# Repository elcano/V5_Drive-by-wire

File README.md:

# V5_Drive-by-wire
Updated code and PCB for light vehicle drive by wire.

This repository is for use with the **Drive by Wire** board created to be used for the ELCANO self-driving tricycle. It controls throttle (Ebike controller), brakes (solenoid) and steering (either linear servo or motor controller board with a linear actuator). All vehicle actions are logged to an SD card, which is the main data for debugging. Vehicle can be controlled by

1) 6-channel Radio Control (RC) unit

2) Operator controls (OP)

3) Vehicle automation computer via CAN. We have demonstrated a Jetson Nano using a Pixhawk to find GNSS points and move from waypoint to waypoint.

In order for this module to run external libraries are required.

Libraries needed are listed below:

Version 4 and 5 (Arduino Due)  _______________________________________________
* Due CAN and CAN Common by Collin Kidder
    https://github.com/collin80/due_can
    https://github.com/collin80/can_common

## To Install

* Download the **Drive_By_Wire** module into the project parent directory
```
git clone https://github.com/elcano/Drive-by-wire.git
```
* Move into the **Drive_By_Wire** folder
```
cd Drive_By_Wire
```
* Download the required libraries
```
git clone https://github.com/SweBarre/MCP48x2.git
git clone https://github.com/ivanseidel/DueTimer.git
git clone https://github.com/collin80/can_common.git
git clone https://github.com/collin80/due_can.git
```
* Add the folders above to the IDE directory. In Windows, add the required libraries to: C:\Users\<username>\Documents\Arduino\libraries
* Arduino Due requires additional installation. On the IDE, go to Tools -> Boards -> Boards Manager -> Arduino SAM Boards (32-bits ARM Cortex-M3) 

## Navigating Arduino IDE: 
* **Selecting Board:** Tools -> Board -> Arduino SAM Boards -> Arduino Due
* **Selecting Serial Port:** Tools -> Port -> COM (Arduino Due)
* **Accessing Serial Monitor:** Right-hand Corner -> Select Baud Rate (115200)

## Drive-by-Wire: 
* **Low-level board code with RC control support with existing code for brakes, steering, and throttle.**

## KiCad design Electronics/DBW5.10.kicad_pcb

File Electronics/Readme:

Full KiCAD project for DBW circuit board

There is a subdirectory for the power box.

The main KiCAD project has lost the link to the schematics. 
The zip file contains the three sheets of as-built schematics as Low_Level4_1_x.kicad.sch

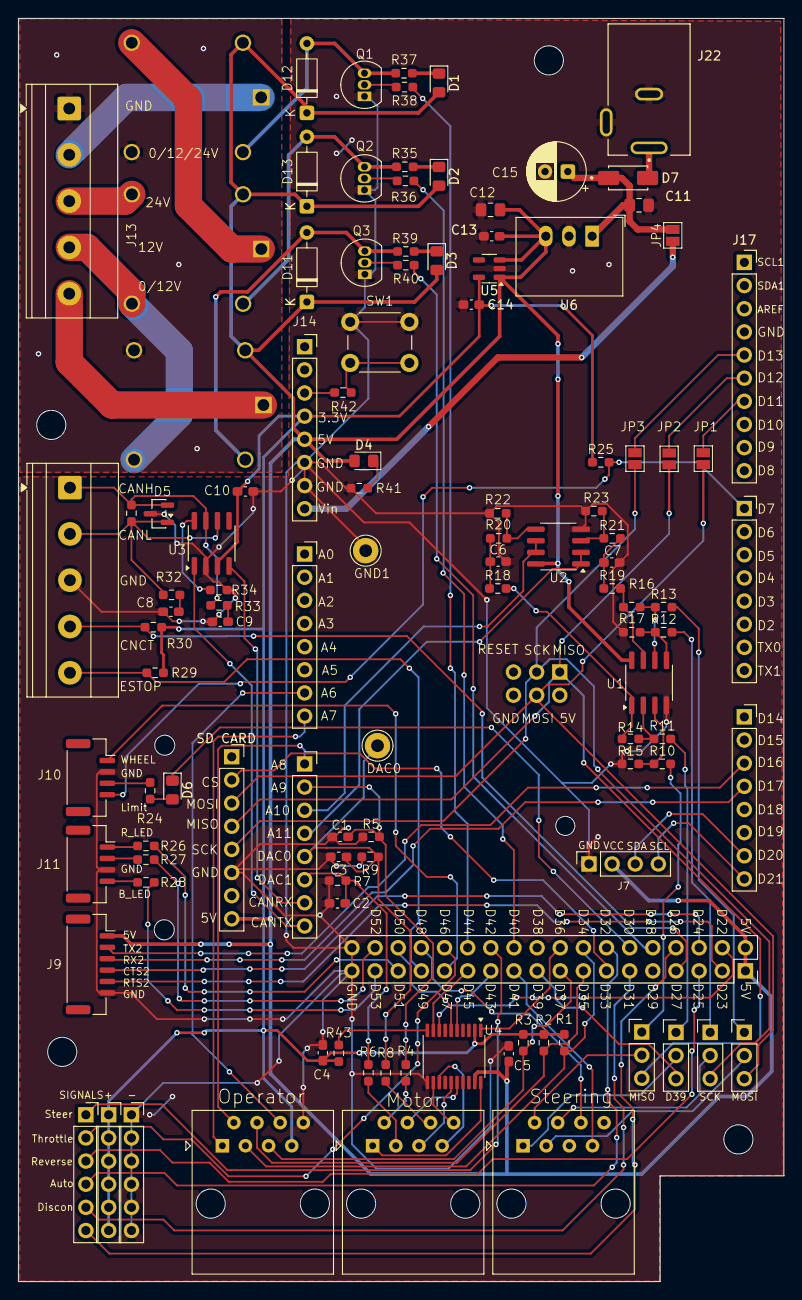
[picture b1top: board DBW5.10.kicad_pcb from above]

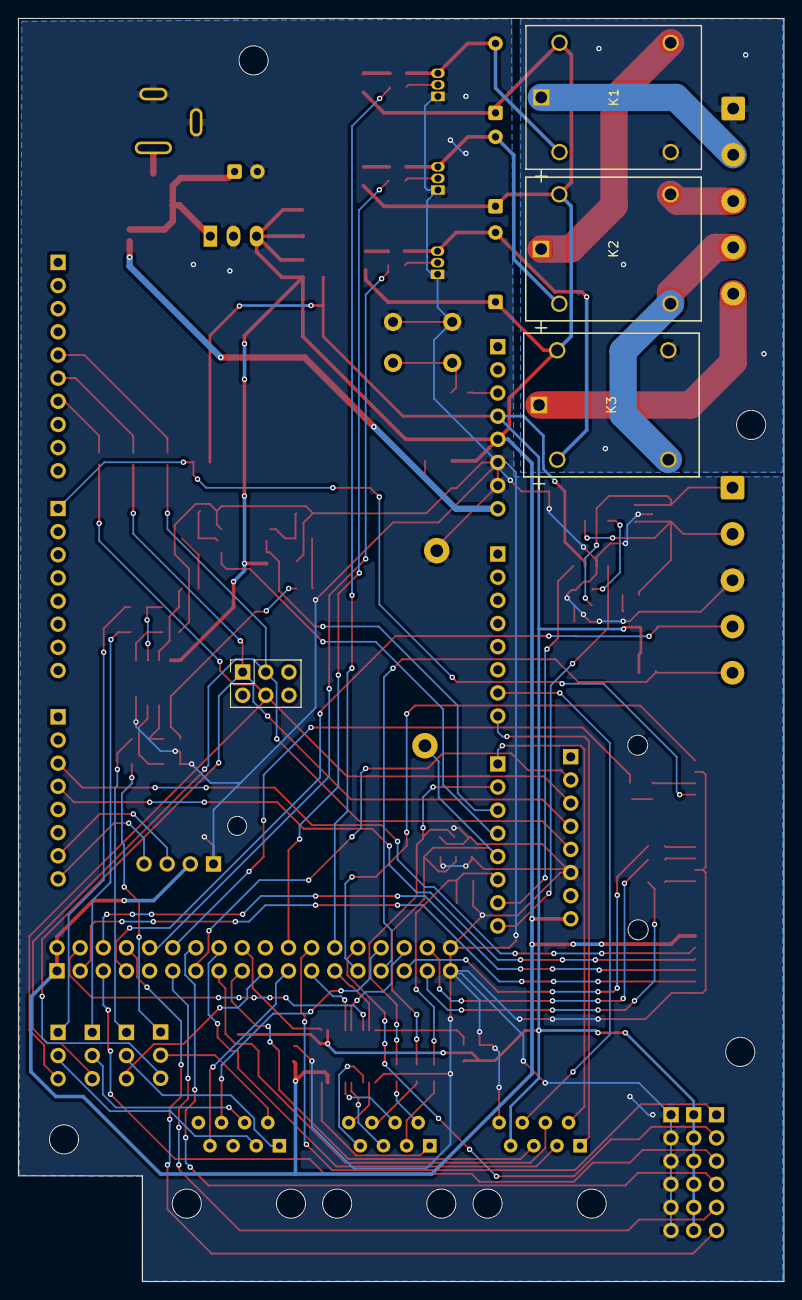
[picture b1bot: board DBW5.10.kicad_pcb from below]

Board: 2 copper layers, 84.0 x 138.6 mm, 113 parts (4 on the bottom side), 112 nets.

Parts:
C1, C2, C3, C4, C5, C10: 0.1uF; C_0603_1608Metric_Pad1.08x0.95mm_HandSolder
C6, C7: 100nF; C_0603_1608Metric_Pad1.08x0.95mm_HandSolder
C8, C9: 100pF; C_0603_1608Metric_Pad1.08x0.95mm_HandSolder
C11, C12: 10uF; C_0805_2012Metric_Pad1.18x1.45mm_HandSolder
C13, C14: 1uF; C_0603_1608Metric_Pad1.08x0.95mm_HandSolder
C15: 47uF; CP_Radial_D6.3mm_P2.50mm
D1, D2, D3: LED; LED_0805_2012Metric_Pad1.15x1.40mm_HandSolder
D4: LED_Power; LED_0805_2012Metric_Pad1.15x1.40mm_HandSolder
D5: NUP2105L; SOT-23
D6: LED_Debug; LED_0805_2012Metric_Pad1.15x1.40mm_HandSolder
D7: B140-13-F; DIOM4326X240N
D11, D12, D13: 1N4148; D_DO-35_SOD27_P7.62mm_Horizontal
DAC0: TestPoint; TestPoint_Loop_D2.60mm_Drill1.4mm_Beaded
GND1: TestPoint; TestPoint_Loop_D2.60mm_Drill1.4mm_Beaded
J1: O-RJ45; RJ45_Amphenol_54602-x08_Horizontal
J2: M-RJ45; RJ45_Amphenol_54602-x08_Horizontal
J3: S-RJ45; RJ45_Amphenol_54602-x08_Horizontal
J4, J5, J6: Conn_01x06; PinSocket_1x06_P2.54mm_Vertical
J7: Conn_01x04; PinSocket_1x04_P2.54mm_Vertical
J8, J14, J15, J16, J18, J19: Conn_01x08; PinSocket_1x08_P2.54mm_Vertical
J9: Conn_01x06; JST_GH_SM06B-GHS-TB_1x06-1MP_P1.25mm_Horizontal
J10, J11: Conn_01x04; JST_GH_SM04B-GHS-TB_1x04-1MP_P1.25mm_Horizontal
J12, J13: Screw_Terminal_01x05; TerminalBlock_Phoenix_MKDS-1,5-5-5.08_1x05_P5.08mm_Horizont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
J17: Conn_01x10; PinSocket_1x10_P2.54mm_Vertical
J20: Conn_02x18_Odd_Even; PinSocket_2x18_P2.54mm_Vertical
J21: Conn_02x03_Odd_Even; PinSocket_2x03_P2.54mm_Vertical
J22: 54-00129; TENSILITY_54-00129
JP1, JP2, JP3, JP4: Jumper_2_Open; SolderJumper-2_P1.3mm_Open_Pad1.0x1.5mm
JP5, JP6, JP7, JP8: Jumper_3_Bridged12; PinHeader_1x03_P2.54mm_Vertical
K1, K2, K3: J107F1CS125VDC.36; RELAY5_J107F-1C_CRS
Q1, Q2, Q3: 2N3904; TO-92_Inline
R1, R2, R3, R22, R23, R25, R29, R30, R34, R43: 10k; R_0603_1608Metric_Pad0.98x0.95mm_HandSolder
R4: 1.5k; R_0603_1608Metric_Pad0.98x0.95mm_HandSolder
R5: 2.7k; R_0603_1608Metric_Pad0.98x0.95mm_HandSolder
R6, R8: 15k; R_0603_1608Metric_Pad0.98x0.95mm_HandSolder
R7, R9: 27k; R_0603_1608Metric_Pad0.98x0.95mm_HandSolder
R10, R11, R12, R13, R14, R15, R16, R17: 22k; R_0603_1608Metric_Pad0.98x0.95mm_HandSolder
R18, R19, R35, R36, R37, R38, R39, R40, R41: 1k; R_0603_1608Metric_Pad0.98x0.95mm_HandSolder
R20, R21: 4.7k; R_0603_1608Metric_Pad0.98x0.95mm_HandSolder
R24: 1K; R_0603_1608Metric_Pad0.98x0.95mm_HandSolder
R26, R27, R28: 150; R_0603_1608Metric_Pad0.98x0.95mm_HandSolder
R31: 120; R_0603_1608Metric_Pad0.98x0.95mm_HandSolder
R32, R33: 22; R_0603_1608Metric_Pad0.98x0.95mm_HandSolder
R42: 100; R_0603_1608Metric_Pad0.98x0.95mm_HandSolder
SW1: SW_Push; SW_PUSH_6mm
U1, U2: LM358; SOIC-8_3.9x4.9mm_P1.27mm
U3: TCAN334G; SOIC-8_3.9x4.9mm_P1.27mm
U4: TXB0108PW; TSSOP-20_4.4x6.5mm_P0.65mm
U5: TLV75533PDBV; SOT-23-5
U6: R-78E5.0-1.0; Converter_DCDC_RECOM_R-78E-0.5_THT

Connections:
3.3V: C4.2, C10.2, C14.1, J1.7, J5.1, J5.2, J5.3, J5.4, J5.5, J5.6, J14.4, R1.1, R2.2, R3.2, R25.1, R29.2, R30.2, R43.1, U3.3 (VCC), U4.2 (V_{CCA}), U5.5 (OUT)
5V: C5.1, C12.1, C13.1, D1.2 (A), D2.2 (A), D3.2 (A), D4.2 (A), D11.1 (K), D12.1 (K), D13.1 (K), J7.2, J8.8, J9.1, J14.5, J20.1, J20.2, K1.5, K2.5, K3.5, U1.8 (V+), U2.8 (V+), U4.19 (V_{CCB}), U5.1 (IN), U5.3 (EN), U6.3 (OUT)
9V: C11.1, C15.1, D7.C, JP4.2 (B), U6.1 (IN)
A6 OP_Center: J1.6, J15.7
A7 OP_Steer: J1.1, J15.8
A8 OP_Throttle: J1.2, J16.1
A9 Moter current: C1.1, J16.2, R4.2, R5.1
A10 L_sense: J16.3, U2.6 (-), U2.7
A11 R_sense: J16.4, U2.1, U2.2 (-)
CANRX: J16.7, U3.4 (RXD)
CANTX: J16.8, U3.1 (TXD)
D7 Gate_limit: J10.4, J18.1, R25.2
D16 Tx2: J9.2, J19.3
D17 Rx2: J9.3, J19.4
D20 SDA: J7.3, J19.7
D21 SCL: J7.4, J19.8
D22 Speedo: J20.4, U4.8 (A7)
D23 RTS2: J9.5, J20.3
D24 CTS2: J9.4, J20.6
D25 FWD/REV_CH3: J4.3, J20.5
D26 RC_CH6: J4.6, J20.8
D27 Connected: J12.4, J20.7, R30.1
D28 Gate raise: J20.10, R40.2
D30 DEBUG_LED: D6.1 (K), J20.12
D31 Disconnect_CH5: J4.5, J20.11
D32 Man/Auto_CH4: J4.4, J20.14
D33 CS_SD: J8.2, J20.13
D34 OP_FWD/REV: J1.3, J20.16, R1.2
D35 OP_Man/Auto: J1.4, J20.15, R2.1
D36 REV: J20.18, U4.1 (A1)
D37 OP_Disconnect: J1.5, J20.17, R3.1
D39 CS/L_Angle: J20.19, JP7.3 (B)
D40 Brake Volt: J20.22, R36.2
D41 L_turn: J3.7, J20.21
D42 Steer_CH1: J4.1, J20.24
D43 Regen: J20.23, U4.5 (A4)
D44 BRAKE_ON: J20.26, R38.2
D45 Ebike power in: J20.25, U4.9 (A8)
D46 Throttle_CH2: J4.2, J20.28
D47 IRPT_WHEEL: J10.1, J20.27
D48 R_turn: J3.6, J20.30
D49 ESTOP: J12.5, J20.29, R29.1
D50 Spare: J20.32, U4.6 (A5)
D51 Red Light: J20.31, R26.2
D52 Green Light: J20.34, R27.2
D53 Blue Light: J20.33, R28.2
DAC0: C3.1, DAC0.1, J16.5, R8.2, R9.1
DAC1: C2.1, J16.6, R6.2, R7.1
GND: J13.1, K1.3, K3.4
GND1: C1.2, C2.2, C3.2, C4.1, C5.2, C6.1, C7.1, C8.1, C9.1, C10.1, C11.2, C12.2, C13.2, C14.2, C15.2, D5.3 (A), GND1.1, J1.8, J6.1, J6.2, J6.3, J6.4, J6.5, J6.6, J7.1, J8.6, J9.6, J10.2, J11.3, J12.3, J14.6, J14.7, J20.35, J20.36, J22.B, J22.C, Q1.1 (E), Q2.1 (E), Q3.1 (E), R5.2, R7.2, R9.2, R15.1, R17.2, R22.2, R23.2, R34.2, R41.1, SW1.1, U1.4 (V-), U2.4 (V-), U3.2 (GND), U4.11 (GND), U5.2 (GND), U6.2 (GND)
MISO: J8.4, J21.1, JP2.1 (A), JP8.3 (B)
MOSI: J8.3, J21.4, JP1.1 (A), JP5.3 (B)
unnamed: C6.2, R18.1, R20.2
unnamed: C7.2, R19.1, R21.2
unnamed: C8.2, R32.1
unnamed: C9.2, R33.1
unnamed: D1.1 (K), R37.1
unnamed: D2.1 (K), R35.1
unnamed: D3.1 (K), R39.1
unnamed: D4.1 (K), R41.2
unnamed: D6.2 (A), R24.2
unnamed: D7.A, J22.A
unnamed: D11.2 (A), K3.2, Q3.3 (C), R39.2
unnamed: D12.2 (A), K1.2, Q1.3 (C), R37.2
unnamed: D13.2 (A), K2.2, Q2.3 (C), R35.2
unnamed: J2.2, R4.1
unnamed: J2.3, R6.1
unnamed: J2.6, R8.1
unnamed: J10.3, R24.1
unnamed: J11.1, R26.1
unnamed: J11.2, R27.1
unnamed: J11.4, R28.1
unnamed: D5.2 (K), J12.1, R31.1, R33.2, U3.7 (CANH)
unnamed: D5.1 (K), J12.2, R31.2, R32.2, U3.6 (CANL)
unnamed: J13.2, K1.1
unnamed: J13.3, K2.4
unnamed: J13.4, K2.3, K3.3
unnamed: J13.5, K3.1
unnamed: J14.8, JP4.1 (A)
unnamed: J17.5, JP3.2 (B)
unnamed: J17.6, JP2.2 (B)
unnamed: J17.7, JP1.2 (B)
unnamed: JP5.1 (A), R13.2
unnamed: J3.3, JP5.2 (C)
unnamed: JP6.1 (A), R12.2
unnamed: J3.4, JP6.2 (C)
unnamed: JP7.1 (A), R11.2
unnamed: J3.1, JP7.2 (C)
unnamed: JP8.1 (A), R10.2
unnamed: J3.2, JP8.2 (C)
unnamed: K1.4, K2.1
unnamed: Q1.2 (B), R38.1
unnamed: Q2.2 (B), R36.1
unnamed: Q3.2 (B), R40.1
unnamed: R14.1, R18.2, U1.1
unnamed: R16.1, R19.2, U1.7
unnamed: R42.1, SW1.2
unnamed: R10.1, R15.2, U1.3 (+)
unnamed: R11.1, R14.2, U1.2 (-)
unnamed: R12.1, R17.1, U1.5 (+)
unnamed: R13.1, R16.2, U1.6 (-)
unnamed: R21.1, R23.1, U2.3 (+)
unnamed: R20.1, R22.1, U2.5 (+)
unnamed: R34.1, U3.8 (STB)
unnamed: J2.1, U4.20 (B1)
unnamed: J2.4, U4.16 (B4)
unnamed: J2.5, U4.15 (B5)
unnamed: J2.7, U4.13 (B7)
unnamed: J2.8, U4.12 (B8)
unnamed: R43.2, U4.10 (OE)
RESET: J14.3, R42.2
SCK: J8.5, J21.3, JP3.1 (A), JP6.3 (B)

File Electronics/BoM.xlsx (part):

|  |  |  | Board Manufacturer Specs
 |  |  | Traces are 15 mil | Board needs 2 oz copper |  | Two Layers: Front & Back
 |  |  |  | Main Through hole components
Qty | unit price | Total price | Device Name | Value | In BoM? | Digikey Part Number | Package | Part Label | Description | DESCRIPTION | External Link | DIGI-KEY_PURCHASE_URL | MANUFACTURER_PART_NUMBER | MF | MP | MPN | OC_FARNELL | OC_NEWARK | PACKAGE | PROD_ID | SF_SKU | SPICEPREFIX | VALUE | VENDOR
8 | 0.007(for buying 10) | 7.0000000000000007E-2 | R_0603_1208 | 22k ohms | yes | 311-22.0KHRCT-ND | Cut Tape (CT) | R10,R11,R13,R12,R14,R15,R16,R17 | Chip Resistor | in stock, 1% tolerance,(1.60mm x 0.80mm)
10 | 6.0000000000000001E-3 | 0.06 | R_0603_1208 | 10k ohms | yes | 311-10.0KHRCT-ND | Cut Tape (CT) | R1,R2,R3,R22,R23,R25,R29,R30,R34,R43 | Chip Resistor | in stock, 1% tolerance,(1.60mm x 0.80mm)
2 | 0.007（for buying 10) | 7.0000000000000007E-2 | R_0603_1208 | 22 ohms | yes | 311-22.0HRCT-ND | Cut Tape (CT) | R32,R33 | Chip Resistor | in stock, 1% tolerance,(1.60mm x 0.80mm)
10 | 8.0000000000000002E-3 | 0.08 | R_0603_1208 | 1k ohms | yes | 311-1.00KHRCT-ND | Cut Tape (CT) | R18,R19,R24,R35,R36,R37,R38,R39,R40,R41 | Chip Resistor | in stock, 1% tolerance,(1.60mm x 0.80mm)
3 | 0.008(for buying 10) | 0.08 | R_0603_1208 | 150 ohms | yes | 311-150HRCT-ND | Cut Tape (CT) | R26,R27,R28 | Chip Resistor | in stock, 1% tolerance,(1.60mm x 0.80mm)
1 | 0.1 | 0.1 | R_0603_1208 | 2.7k ohms | yes | 311-2.70KHRCT-ND | Cut Tape (CT) | R5 | Chip Resistor | in stock, 1% tolerance,(1.60mm x 0.80mm)
1 | 0.1 | 0.1 | R_0603_1208 | 1.5k ohms | yes | 13-RC0603FR-101K5LCT-ND | Cut Tape (CT) | R4 | Chip Resistor | in stock, 1% tolerance,(1.60mm x 0.80mm)
1 | 0.1 | 0.1 | R_0603_1208 | 120 ohms | yes | 311-120HRCT-ND | Cut Tape (CT) | R31 | Chip Resistor | in stock, 1% tolerance,(1.60mm x 0.80mm)
2 | 0.006(for buying 10) | 0.06 | R_0603_1208 | 15k ohms | yes | RMCF0603FG15K0CT-ND | Cut Tape (CT),RMCF | R6,R8 | Chip Resistor | in stock, 1% tolerance,(1.55mm x 0.80mm)
2 | 0.009(for buying10) | 0.09 | R_0603_1208 | 27k ohms | yes | 13-RC0603FR-1327KLCT-ND | Cut Tape (CT) | R7,R9 | Chip Resistor | in stock, 1% tolerance,(1.60mm x 0.80mm)
2 | 0.007(for buying 10) | 7.0000000000000007E-2 | R_0603_1208 | 4.7k ohms | yes | 311-4.70KHRCT-ND | Cut Tape (CT) | R20,R21 | Chip Resistor | in stock, 1% tolerance,(1.60mm x 0.80mm)
1 | 0.1 | 0.1 | R_0603_1208 | 100 ohms | yes | 311-100HRCT-ND | Cut Tape (CT) | R42 | Chip Resistor | in stock, 1% tolerance,(1.60mm x 0.80mm)
3 | 0.71 | 2.13 | RJ_45 |  | yes | 609-1046-ND | Modular/Ethernet Connector (RJ45, RJ11) Jacks | J1,J2,J3 | RJ45 | in stock,
3 | 0.42 | 1.26 | Pinheader-1x6 |  | yes | S7004-ND |  | J4,J5,J6 | Pin connector(female) | IC REG LINEAR 3.3V 1A DPAK
1 | 0.38 | 0.38 | Pinheader-1x4 |  | yes | S7037-ND |  | J7 | Pin connector(female)
1 | 0.51 | 0.51 | Pinheader-1x8 |  | yes | S7006-ND |  | J8 | Pin connector(female)
1 | 0.48 | 0.48 | JST Pinheader-1x6 |  | yes | 455-1568-1-ND |  | J9 | CONN HEADER SMD R/A 6POS 1.25MM | Connector Header Surface Mount, Right Angle 6 position 0.049" (1.25mm)
2 | 0.38 | 0.76 | JST Pinheader-1x4 |  | yes | 455-1566-1-ND |  | J10,J11 | CONN HEADER SMD R/A 4POS 1.25MM | Connector Header Surface Mount, Right Angle 4 position 0.049" (1.25mm)
2 | 1.84 | 3.68 | Screw-terminal-1x5 |  | yes | 2861-ELK508V-05P-ND |  | J12,J13 | Screw terminal | TERM BLK 5POS 180DEG 5.08MM PCB, Max current is 13.5A,V 300V
5 | 0.49 | 2.4500000000000002 | Stacking Pinheader-1x8 |  | yes | HDR100IMP08F-G-V-ST |  | J14,J15,J16,J18,J19 | 0.1" 8 PIN VERTICAL FEMALE STACK | 8 Position Header Connector 0.100" (2.54mm) Through Hole Gold
1 | 5(include 6) | 5 | Stacking Pinheader-1x10 |  | yes | 920-0087-01 |  | J17 | CONN HDR 10POS 0.1 GLD PCB 1=6PC | 10 Position Header Connector 0.100" (2.54mm) Through Hole Gold
1 | 0.49 | 0.98 | Stacking Pinheader-2x18 | Uses 2 1x8 and 2 1x10 | yes | HDR100IMP08F-G-V-ST & 920-0087-01 |  | J20 | using two 1x8 and two 1x10 | The price here is for the 1x8 version. For the 1x10 version, it already include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
1 | 0.49 | 0.49 | Stacking Pinheader-2x3 |  | yes | S7106-ND |  | J21 | CONN HDR 6POS 0.1 GOLD PCB | 6 Position Header Connector 0.100" (2.54mm) Through Hole Gold
1 | 0.91 | 0.91 | Jack DC power |  | yes | 839-54-00129-ND |  | J22 | Jack DC power supply | Power Barrel Connector Jack 2.10mm ID (0.083"), 5.50mm OD (0.217") Through Hole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
4 | 0.12 | 0.48 | Jumpers |  | yes | 732-5316-ND |  | JP5,JP6,JP7,JP8 | Jumpers using Connector Header | Connector Header Through Hole 3 position 0.100" (2.54mm)
 |  |  |  | Capcitors
Qty |  |  | Device Name | Value | In BoM? | Digikey Part Number | Package | Part Label | Description | DESCRIPTION | External Link | DIGI-KEY_PURCHASE_URL | MANUFACTURER_PART_NUMBER | MF | MP | MPN | OC_FARNELL | OC_NEWARK | PACKAGE | PROD_ID | SF_SKU | SPICEPREFIX | VALUE | VENDOR
8 | 0.011(buying for 10) | 0.11 | Capcitors | 0.1uF | yes | 399-C0603C104K5RACTUCT-ND |  | C1,C2,C3,C4,C5,C6,C7,C10 | CAP CER 0.1UF 50V X7R 0603 | 0.1 µF ±10% 50V Ceramic Capacitor X7R 0603 (1608 Metric)
2 | 0.1 | 0.2 | Capcitors | 100pF | yes | 399-C0603C101K5RACTUCT-ND |  | C8,C9 | CAP CER 100PF 50V X7R 0603 | 100 pF ±10% 50V Ceramic Capacitor X7R 0603 (1608 Metric)
2 |  |  | Capcitors | 1uF | yes | 399-C0603C105K4RACTUCT-ND |  | C13,C14 | CAP CER 1UF 16V X7R 0603 | 1 µF ±10% 16V Ceramic Capacitor X7R 0603 (1608 Metric)
1 |  |  | Capcitors | 10uF | yes |  |  | C11,C12 | CAP CER 2.2UF 50V X5R 0603 | 2.2 µF ±10% 50V Ceramic Capacitor X5R 0603 (1608 Metric)
 |  |  | Capcitors |  | yes | 478-8875-1-ND |  | C13,C14 | Capacitor polarized | 10 µF Molded Tantalum Capacitors 16 V 1206 (3216 Metric) 3Ohm
1 | 0.19 | 0.19 | Capcitors | 47uF | yes | 399-ESS476M025AE2EACT-ND |  | C16 | Aluminum Electrolytic Capacitors | 47 µF 25 V Aluminum Electrolytic Capacitors Radial, Can 1000 Hrs @ 105°C
 |  |  |  | Other Components
Qty |  |  | Device Name | Value | In BoM? | Digikey Part Number | Package | Part Label | Description | DESCRIPTION | External Link | DIGI-KEY_PURCHASE_URL | MANUFACTURER_PART_NUMBER | MF | MP | MPN | OC_FARNELL | OC_NEWARK | PACKAGE | PROD_ID | SF_SKU | SPICEPREFIX | VALUE | VENDOR
2 | 0.46 | 0.92 | LM358D |  | yes | 497-18378-ND |  | U1,U2 | LM358D | Standard (General Purpose) Amplifier 2 Circuit 8-SOIC
1 | 3.19 | 3.19 | TCAN334G |  | yes | 296-49940-1-ND | Cut Tape (CT) | U3 | TCAN334G | 1/1 Transceiver CANbus 8-SOIC
1 | 1.82 | 1.82 | TXB0108PWR |  | yes | 296-21527-1-ND | Cut Tape (CT) | U4 | Level shifter 5--3.3V | Voltage Level Translator Bidirectional 1 Circuit 8 Channel 100Mbps 20-TSSOP
1 | 0.52 | 0.52 | NCP1117 |  | yes | NCP1117DT33T5GOSCT-ND |  | U5 | Voltage regulator 5--3.3V | Linear Voltage Regulator IC Positive Fixed 1 Output 1A DPAK
1 | 0.54 | 0.54 | LP2985 |  | yes | 296-26128-1-ND |  | U6 | Voltage regulator --5V | Linear Voltage Regulator IC Positive Fixed 1 Output 150mA SOT-23-5
3 | 0.14000000000000001 | 0.42 | 2N3904 |  | yes | 4878-2N3904CT-ND |  | Q1,Q2,Q3 | BJT | Bipolar (BJT) Transistor NPN 40 V 200 mA 300MHz 625 mW Through Hole TO-92
3 | 0.15 | 0.45 | LED |  | yes | 475-LGR971-KN-1CT-ND |  | D1,D2,D3 | LED light for relays | LED GREEN DIFFUSED 0805 SMD
1 | 0.15 | 0.15 | LED |  | yes | 475-LSR976-NR-1CT-ND |  | D4 | LED light for power | LED RED DIFFUSED 0805 SMD
1 | 0.15 | 0.15 | LED |  | yes | 475-LYR976-PS-36-0-20-R18CT-ND |  | D6 | LED light for debug | LED YELLOW DIFFUSED 0805 SMD
1 | 0.17 | 0.17 | NUP2105L |  | yes | 4878-NUP2105LCT-ND |  | D5 | TVS DIODE 24VWM 44VC SOT233 | 44V Clamp 8A (8/20µs) Ipp Tvs Diode Surface Mount SOT-23-3 (TO-236)
1 | 0.2 | 0.2 | D-Schottky |  | yes | B140-FDICT-ND |  | D7 | DIODE SCHOTTKY 40V 1A SMA | DIODE SCHOTTKY 40V 1A SMA
3 | 0.1 | 0.3 | Diode |  | yes | 1N4148FSCT-ND | Cut Tape (CT) | D11,D12,D13 | DIODE STANDARD 100V 200MA DO35 | Diode 100 V 200mA Through Hole DO-35
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
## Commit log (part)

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2025-11-20 Rewrite of version 4 drive by wire
    Numerous changes
2025-11-20 Exclude settings.h
    Data in settingtemplates.h varies from vehicle to vehicle. Copy it, modify it. Name it settings.h, but never put the file in the repository.
2025-11-20 Create StateTransitions.txt
    Text for State transition on Manual/Automatic. The .png file goes with this
2025-11-20 High level organization of trike components
2025-11-20 Diagram to go with State transitions.txt
2025-11-20 Create directory
2025-11-20 Move to folder
2025-11-20 remove directory
2025-11-20 Move file
2026-01-07 Add files via upload
    New diagram and more information on steering connector
2026-01-07 Pins and connectors for DBW board
2026-01-26 Data logger expanded to serial and CAN
    Implemented send CAN and changed all speeds to cm/s
2026-03-31 Revert "Add files via upload"
    This reverts commit dd97e00fde79939bf5d0fab4dc0e221287a8ad8c.
    files put in wrong directory
2026-03-31 Put updates in right directory
    Files were placed in main directory instead of
2026-04-04 Add SetTime utility sketch for DS1307 RTC
2026-04-08 Fix RC control and logger bugs found during hardware testing
2026-04-10 corrected settings for op_estop and enabled
2026-04-16 Fix Operator Joystick Control Bugs
    This PR fixes several bugs found during bench testing with the operator
    joystick on the Yellow Trike (Vehicle 02), with no vehicle connected.
    The joystick inputs were not being processed correctly in OPERATOR_MODE
    and the data log was showing garbage values.
    Bug 1 - Joystick throttle and steering had no effect:
    In OPERATOR_MODE the system ignored all joystick inputs. The code was
2026-04-21 Rename Drive-by_wire to Drive_By_Wire
2026-04-21 Fix Bridge board compatibility: CAN receive, serial logging, USB port
    - receiveCan(): handle 0x100 (speed/brake) and 0x350 (angle) separately;
    set canActive=true on receipt; watchFor() calls moved to constructor
    - update(): skip RC overwrite of desired values when canActive is set
    - RC_Controller: INITIALIZING falls through to AUTO_RC when no RC/operator
    - Logger: disable RTC init via HAS_RTC define (enabled by default);
    guard first_time Serial debug block with #ifndef USE_NATIVE_USB
2026-04-22 Adopt new Elcano CAN protocol for HiDrive/HiStatus
    Swap 0x100 and 0x350 to match the updated wiki protocol
    (elcanoproject.org/wiki/Communication): 0x350 HiDrive now carries
    speed/brake/angle, and 0x100 HiStatus carries a status-bit byte
    (0x80 e-stop, 0x40 autonomous, 0x04 reverse). Emit 0x200 LowStatus
    mirroring DBW's current mode so the Nav board can observe it. Add
    0x250/0x251 and 0x4C0 IDs to Can_Protocol.h for completeness.
2026-04-23 Create Electronics folder
2026-04-23 Full ZIP file
2026-04-25 Fix RC channel ordering bug - uncomment channel swap in getMappedValue
    CHANGES: 1) Removed the early return statement on line 206 that was preventing the channel swap code from executing. 2) Uncommented lines 207-210 to enable the channel index swap. The RC_Controller w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
2026-05-12 Added auto e-stop
2026-05-16 Update DBW for new CAN protocol and always-on CAN log emit
    - 0x350 receive: read brake as uint8 byte 2 and buffer the new mode byte,
    matching the current wiki spec.
    - Logger CAN emit: always run every loop tick (was a fallback only when
    SD failed), so any bus listener (Sensor Hub, future Jetson) can record
    the log stream. SD and serial logging remain as optional independent
    sinks.
2026-06-05 Map L_TURN/R_TURN to bridge wiring (D26/D28); disable CH6 collision
    DBW now drives the steering direction signals on the pins that are
    physically wired through to Router on the Bridge board (per Minhee):
    LEFT_TURN_PIN = D26 -> Router D4
    RIGHT_TURN_PIN = D28 -> Router D2
    Pin 26 is shared with CH6_PIN in DBW_Pins.h. Since RC channel 6 is
    reserved/unused on this trike, disable CH6's pinMode(INPUT) and the
2026-06-05 Closed-loop steering against CAN-supplied wheel-angle feedback
    Replace the servo-pulse / motor-controller steering path with a
    two-wire digital direction scheme matching the bridge wiring. Each
    loop, SteeringPID asserts at most one of LEFT_TURN / RIGHT_TURN
    based on the sign of the error against the measured wheel angle:
    Nav -> 0x350 desired_angle -> DBW SteeringPID:
    err = desired - measured
2026-06-05 Bypass throttle PID when desired speed is zero
    When Nav (or any other commander) requests speed=0, call Stop()
    directly instead of running ThrottlePID(0). The PID accumulates a
    positive integral during cruise; running PID(0) afterward keeps
    PIDThrottle above PID_COAST, the ACCEL branch fires and releases
    the brakes, and DAC0 stays above zero. In the simulator this means
    Router keeps reading "throttle on" and the trike never actually
2026-06-06 Simplify open-loop steering fallback to fixed-step
    Replace the time-rate slew (200 degX10/sec scaled by dt_ms) in the
    haveMeasured==false branch of SteeringController::update() with a fixed
    +/-20 degX10 step per loop, matching Router's ANGLE_CHANGE_TENTHS
    directly. Removes the millis() read, the dt math, and the
    lastUpdate_ms member.
    The fallback only runs in degraded environments (sim without 0x430
